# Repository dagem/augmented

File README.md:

# Augmented
an hhkb style keyboard with an added macro row

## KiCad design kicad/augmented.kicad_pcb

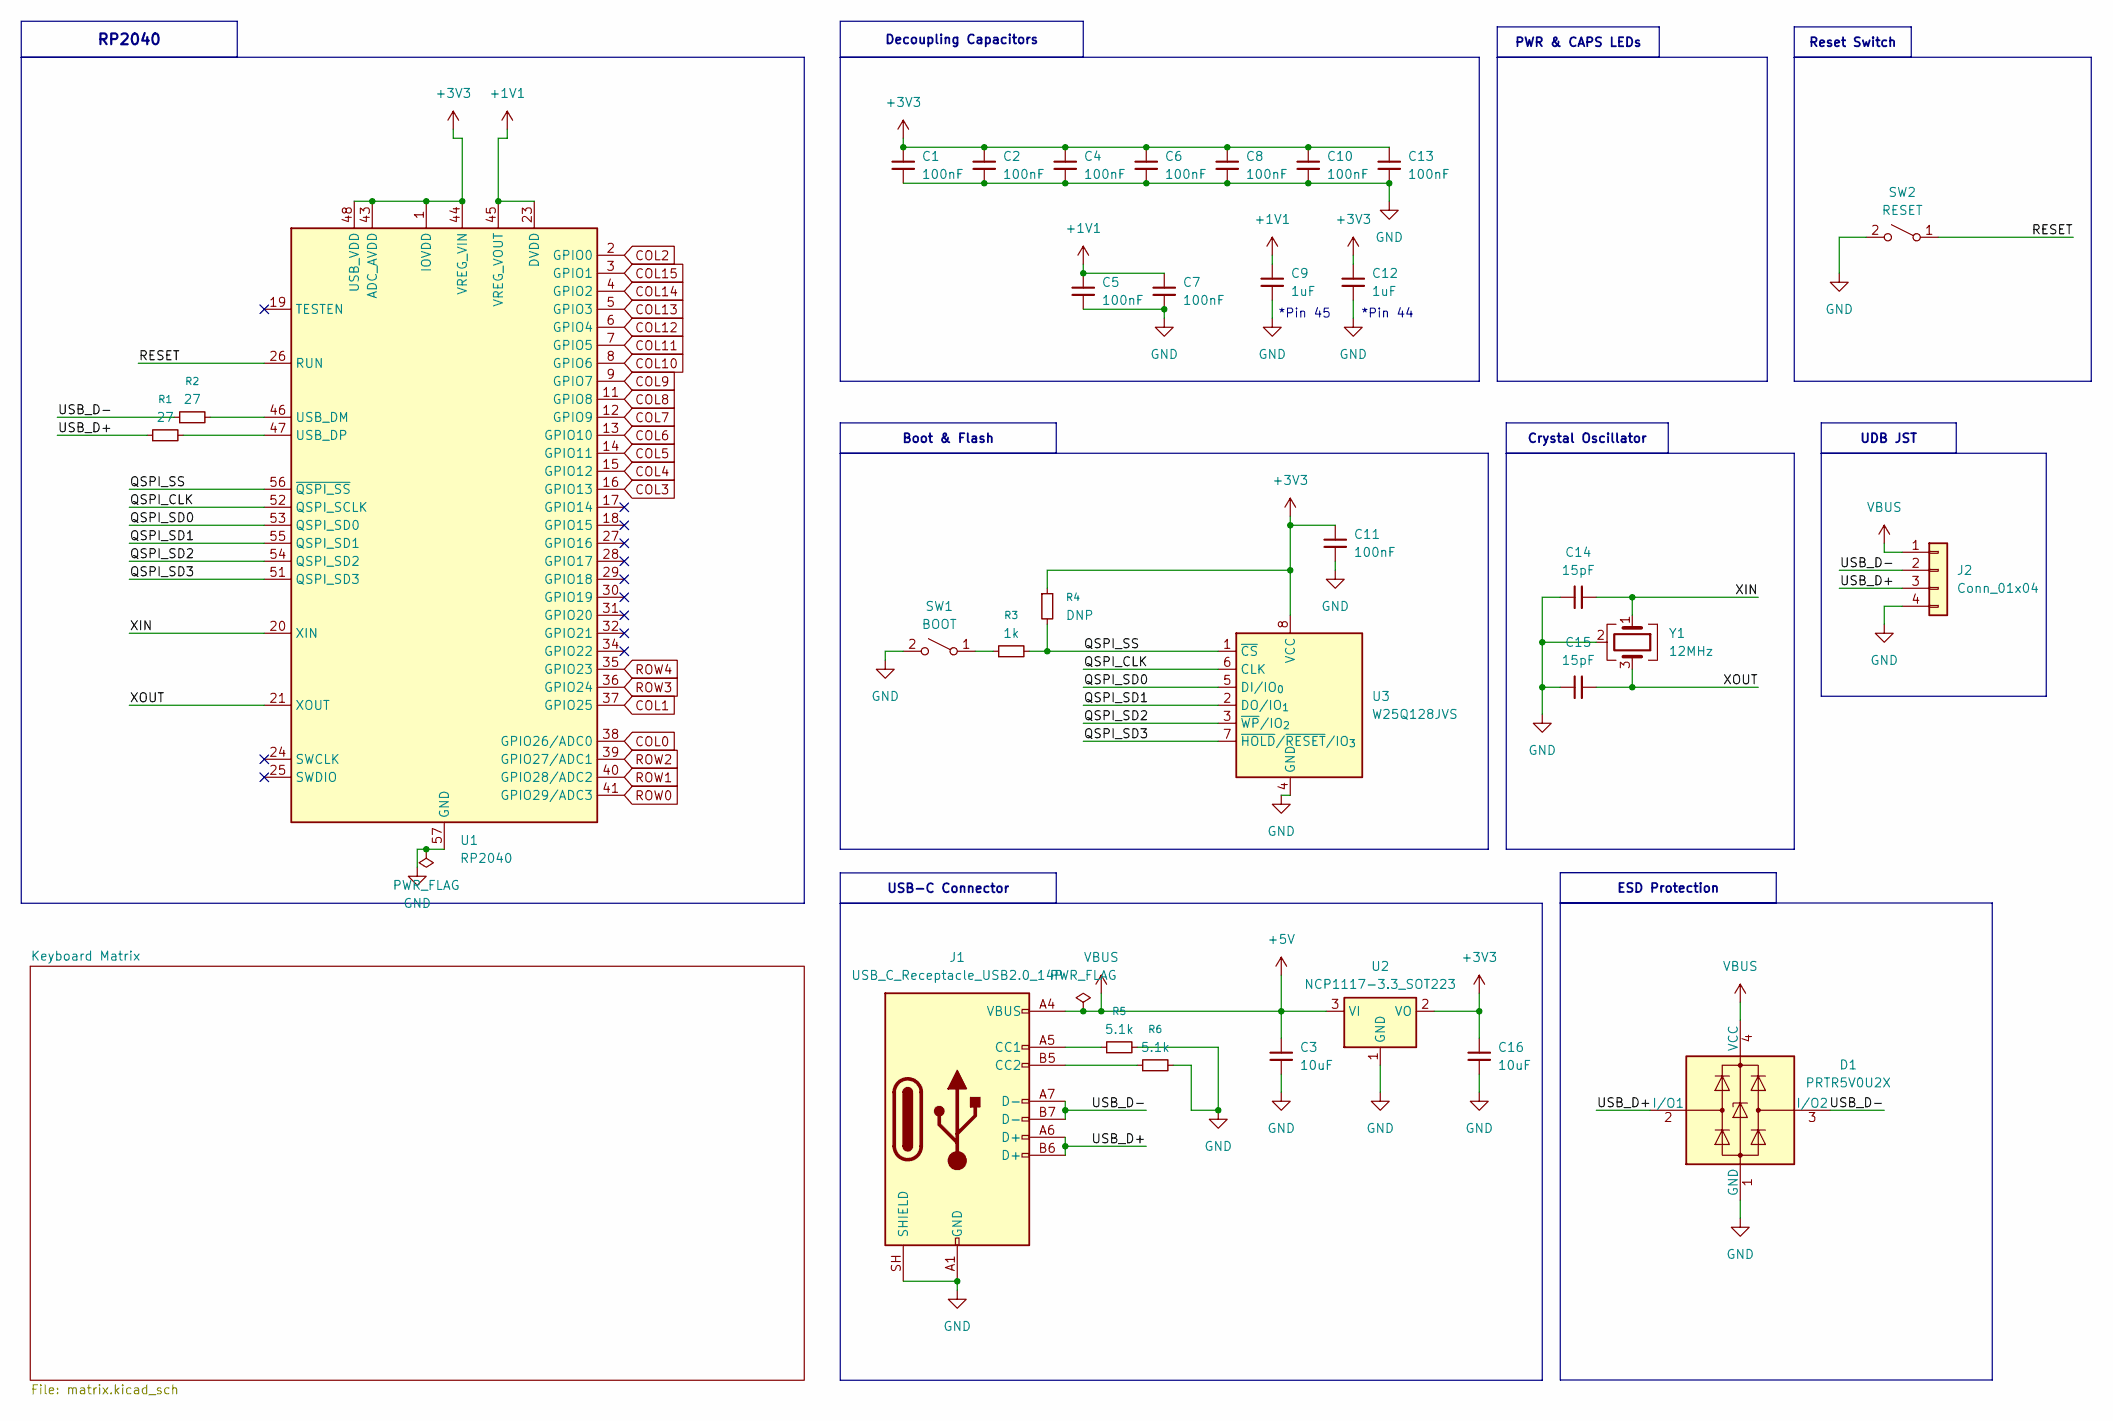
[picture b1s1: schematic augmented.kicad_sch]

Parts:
C1, C2, C4, C5, C6, C7, C8, C10, C11, C13: 100nF; C_0402_1005Metric
C3, C16: 10uF; C_0402_1005Metric
C9, C12: 1uF; C_0402_1005Metric
C14, C15: 15pF; C_0402_1005Metric
D1: PRTR5V0U2X; SOT-143
J1: USB_C_Receptacle_USB2.0_14P; USB_C_Receptacle_HRO_TYPE-C-31-M-12
J2: Conn_01x04; JST_GH_SM04B-GHS-TB_1x04-1MP_P1.25mm_Horizontal
R1, R2: 27; R_0402_1005Metric
R3: 1k; R_0402_1005Metric
R4: DNP; R_0402_1005Metric
R5, R6: 5.1k; R_0402_1005Metric
SW1: BOOT; SW_SPST_SKQG_WithoutStem
SW2: RESET; SW_SPST_SKQG_WithoutStem
U1: RP2040; QFN-56-1EP_7x7mm_P0.4mm_EP3.2x3.2mm
U2: NCP1117-3.3_SOT223; SOT-223-3_TabPin2
U3: W25Q128JVS; SOIC-8_5.3x5.3mm_P1.27mm
Y1: 12MHz; Crystal_SMD_Abracon_ABM8AIG-4Pin_3.2x2.5mm

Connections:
+1V1: C5.1, C7.1, C9.1, U1.23 (DVDD), U1.45 (VREG_VOUT), U1.50 (DVDD)
+3V3: C1.1, C2.1, C4.1, C6.1, C8.1, C10.1, C11.1, C12.1, C13.1, C16.1, R4.1, U1.1 (IOVDD), U1.10 (IOVDD), U1.22 (IOVDD), U1.33 (IOVDD), U1.42 (IOVDD), U1.43 (ADC_AVDD), U1.44 (VREG_VIN), U1.48 (USB_VDD), U1.49 (IOVDD), U2.2 (VO), U3.8 (VCC)
+5V: C3.1, D1.4 (VCC), J1.A4 (VBUS), J1.A9 (VBUS), J1.B4 (VBUS), J1.B9 (VBUS), J2.1, U2.3 (VI)
/QSPI_CLK: U1.52 (QSPI_SCLK), U3.6 (CLK)
/QSPI_SD0: U1.53 (QSPI_SD0), U3.5 (DI/IO_{0})
/QSPI_SD1: U1.55 (QSPI_SD1), U3.2 (DO/IO_{1})
/QSPI_SD2: U1.54 (QSPI_SD2), U3.3 (~WP/IO_{2})
/QSPI_SD3: U1.51 (QSPI_SD3), U3.7 (~HOLD/~RESET/IO_{3})
/QSPI_SS: R3.2, R4.2, U1.56 (~QSPI_SS), U3.1 (~CS)
/RESET: SW2.1 (A), U1.26 (RUN)
/USB_D+: D1.2 (I/O1), J1.A6 (D+), J1.B6 (D+), J2.3, R1.1
/USB_D-: D1.3 (I/O2), J1.A7 (D-), J1.B7 (D-), J2.2, R2.1
/XIN: C14.2, U1.20 (XIN), Y1.1
/XOUT: C15.2, U1.21 (XOUT), Y1.3
COL0: U1.38 (GPIO26/ADC0); also elsewhere on the board
COL1: U1.37 (GPIO25); also elsewhere on the board
COL2: U1.2 (GPIO0); also elsewhere on the board
COL3: U1.16 (GPIO13); also elsewhere on the board
COL4: U1.15 (GPIO12); also elsewhere on the board
COL5: U1.14 (GPIO11); also elsewhere on the board
COL6: U1.13 (GPIO10); also elsewhere on the board
COL7: U1.12 (GPIO9); also elsewhere on the board
COL8: U1.11 (GPIO8); also elsewhere on the board
COL9: U1.9 (GPIO7); also elsewhere on the board
COL10: U1.8 (GPIO6); also elsewhere on the board
COL11: U1.7 (GPIO5); also elsewhere on the board
COL12: U1.6 (GPIO4); also elsewhere on the board
COL13: U1.5 (GPIO3); also elsewhere on the board
COL14: U1.4 (GPIO2); also elsewhere on the board
COL15: U1.3 (GPIO1); also elsewhere on the board
GND: C1.2, C2.2, C3.2, C4.2, C5.2, C6.2, C7.2, C8.2, C9.2, C10.2, C11.2, C12.2, C13.2, C14.1, C15.1, C16.2, D1.1 (GND), J1.A1 (GND), J1.A12 (GND), J1.B1 (GND), J1.B12 (GND), J1.SH (SHIELD), J2.4, R5.2, R6.2, SW1.2 (B), SW2.2 (B), U1.57 (GND), U2.1 (GND), U3.4 (GND), Y1.2 (G), Y1.4 (G)
unnamed: J1.A5 (CC1), R5.1
unnamed: J1.B5 (CC2), R6.1
unnamed: R3.1, SW1.1 (A)
unnamed: R2.2, U1.46 (USB_DM)
unnamed: R1.2, U1.47 (USB_DP)
ROW0: U1.41 (GPIO29/ADC3); also elsewhere on the board
ROW1: U1.40 (GPIO28/ADC2); also elsewhere on the board
ROW2: U1.39 (GPIO27/ADC1); also elsewhere on the board
ROW3: U1.36 (GPIO24); also elsewhere on the board
ROW4: U1.35 (GPIO23); also elsewhere on the board

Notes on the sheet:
*Pin 44
*Pin 45
Boot & Flash
Crystal Oscillator
ESD Protection
USB-C Connector
Reset Switch
PWR & CAPS LEDs
RP2040
UDB JST
Decoupling Capacitors

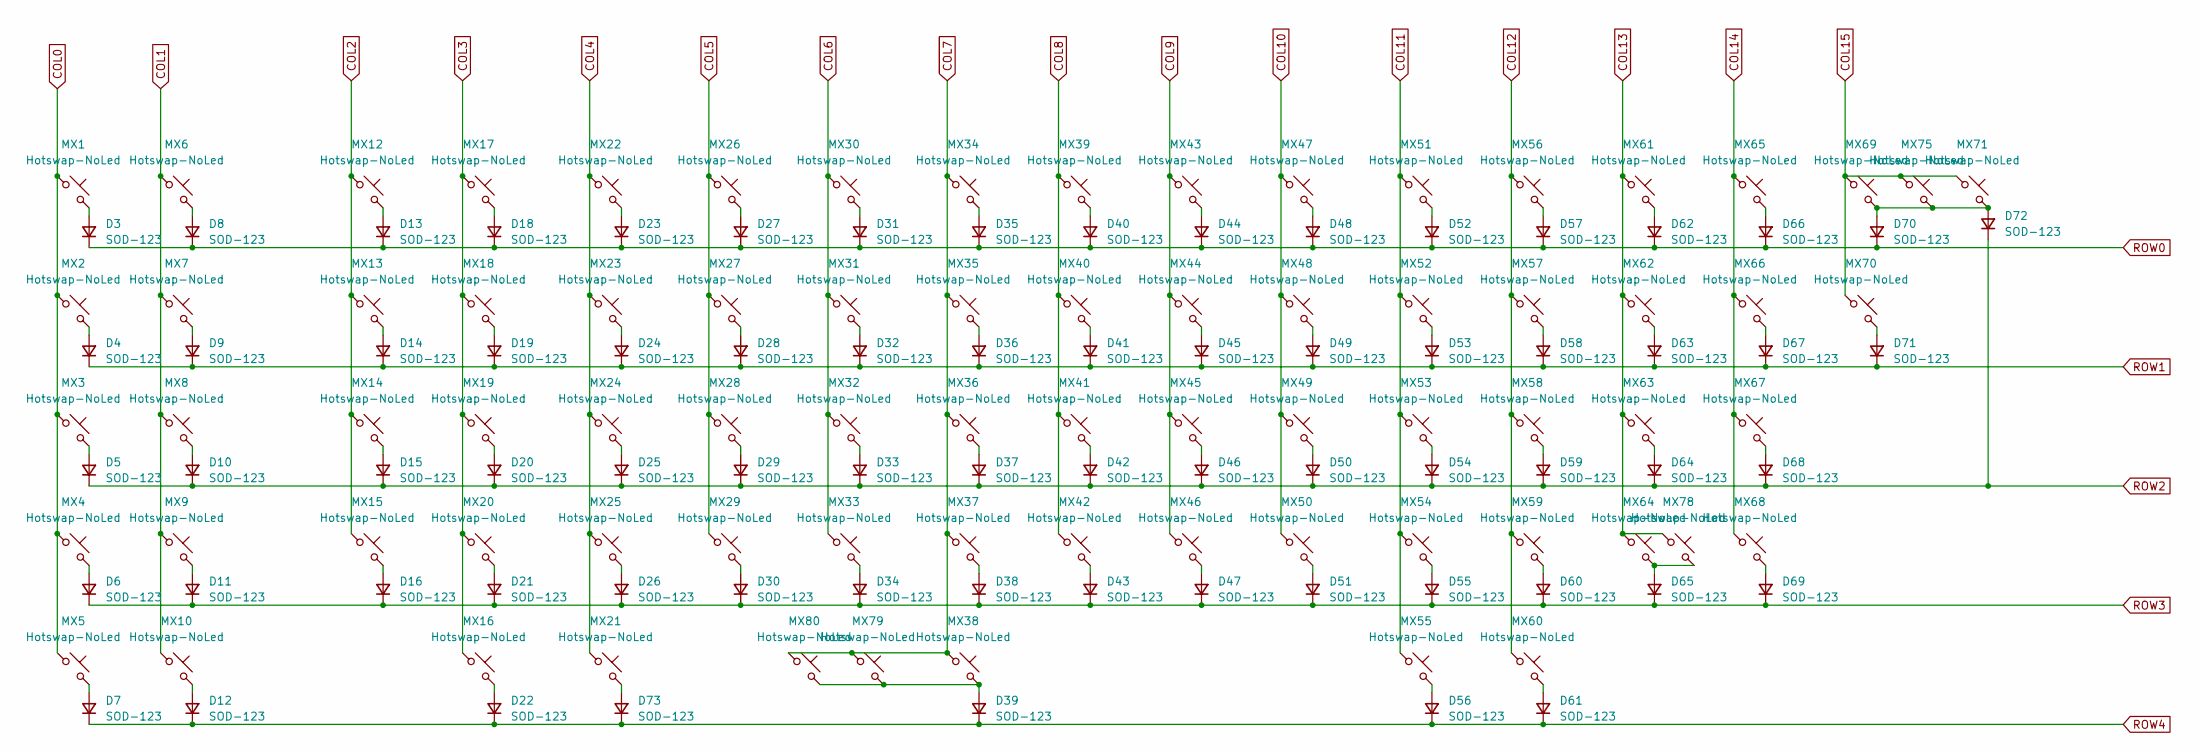
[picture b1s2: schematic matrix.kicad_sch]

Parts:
D3, D4, D5, D6, D7, D8, D9, D10, D11, D12, D13, D14, D15, D16, D18, D19, D20, D21, D22, D23, D24, D25, D26, D27, D28, D29, D30, D31, D32, D33, D34, D35, D36, D37, D38, D39, D40, D41, D42, D43, D44, D45, D46, D47, D48, D49, D50, D51, D52, D53, D54, D55, D56, D57, D58, D59, D60, D61, D62, D63, D64, D65, D66, D67, D68, D69, D70, D71, D72, D73: SOD-123; D_SOD-123
MX1, MX2, MX3, MX4, MX5, MX6, MX7, MX8, MX9, MX10, MX12, MX16, MX17, MX18, MX19, MX20, MX22, MX23, MX24, MX25, MX26, MX27, MX28, MX29, MX30, MX31, MX32, MX33, MX34, MX35, MX36, MX37, MX39, MX40, MX41, MX42, MX43, MX44, MX45, MX46, MX47, MX48, MX49, MX50, MX51, MX52, MX53, MX54, MX56, MX57, MX58, MX59, MX60, MX61, MX62, MX63, MX65, MX66, MX68, MX69, MX71: Hotswap-NoLed; MX-Hotswap-1U
MX13, MX21, MX55, MX70: Hotswap-NoLed; MX-Hotswap-1.5U
MX14, MX64: Hotswap-NoLed; MX-Hotswap-1.75U
MX15, MX67: Hotswap-NoLed; MX-Hotswap-2.25U
MX38: Hotswap-NoLed; MX-Hotswap-6U
MX75: Hotswap-NoLed; MX-Hotswap-2U
MX78: Hotswap-NoLed; MX-Hotswap-2.75U
MX79, MX80: Hotswap-NoLed; MX-Hotswap-3U

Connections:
COL0: MX1.1, MX2.1, MX3.1, MX4.1, MX5.1; also elsewhere on the board
COL1: MX6.1, MX7.1, MX8.1, MX9.1, MX10.1; also elsewhere on the board
COL2: MX12.1, MX13.1, MX14.1, MX15.1; also elsewhere on the board
COL3: MX16.1, MX17.1, MX18.1, MX19.1, MX20.1; also elsewhere on the board
COL4: MX21.1, MX22.1, MX23.1, MX24.1, MX25.1; also elsewhere on the board
COL5: MX26.1, MX27.1, MX28.1, MX29.1; also elsewhere on the board
COL6: MX30.1, MX31.1, MX32.1, MX33.1; also elsewhere on the board
COL7: MX34.1, MX35.1, MX36.1, MX37.1, MX38.1, MX79.1, MX80.1; also elsewhere on the board
COL8: MX39.1, MX40.1, MX41.1, MX42.1; also elsewhere on the board
COL9: MX43.1, MX44.1, MX45.1, MX46.1; also elsewhere on the board
COL10: MX47.1, MX48.1, MX49.1, MX50.1; also elsewhere on the board
COL11: MX51.1, MX52.1, MX53.1, MX54.1, MX55.1; also elsewhere on the board
COL12: MX56.1, MX57.1, MX58.1, MX59.1, MX60.1; also elsewhere on the board
COL13: MX61.1, MX62.1, MX63.1, MX64.1, MX78.1; also elsewhere on the board
COL14: MX65.1, MX66.1, MX67.1, MX68.1; also elsewhere on the board
COL15: MX69.1, MX70.1, MX71.1, MX75.1; also elsewhere on the board
unnamed: D3.2 (A), MX1.2
unnamed: D4.2 (A), MX2.2
unnamed: D5.2 (A), MX3.2
unnamed: D6.2 (A), MX4.2
unnamed: D7.2 (A), MX5.2
unnamed: D8.2 (A), MX6.2
unnamed: D9.2 (A), MX7.2
unnamed: D10.2 (A), MX8.2
unnamed: D11.2 (A), MX9.2
unnamed: D12.2 (A), MX10.2
unnamed: D13.2 (A), MX12.2
unnamed: D14.2 (A), MX13.2
unnamed: D15.2 (A), MX14.2
unnamed: D16.2 (A), MX15.2
unnamed: D18.2 (A), MX17.2
unnamed: D19.2 (A), MX18.2
unnamed: D20.2 (A), MX19.2
unnamed: D21.2 (A), MX20.2
unnamed: D22.2 (A), MX16.2
unnamed: D23.2 (A), MX22.2
unnamed: D24.2 (A), MX23.2
unnamed: D25.2 (A), MX24.2
unnamed: D26.2 (A), MX25.2
unnamed: D27.2 (A), MX26.2
unnamed: D28.2 (A), MX27.2
unnamed: D29.2 (A), MX28.2
unnamed: D30.2 (A), MX29.2
unnamed: D31.2 (A), MX30.2
unnamed: D32.2 (A), MX31.2
unnamed: D33.2 (A), MX32.2
unnamed: D34.2 (A), MX33.2
unnamed: D35.2 (A), MX34.2
unnamed: D36.2 (A), MX35.2
unnamed: D37.2 (A), MX36.2
unnamed: D38.2 (A), MX37.2
unnamed: D39.2 (A), MX38.2, MX79.2, MX80.2
unnamed: D40.2 (A), MX39.2
unnamed: D41.2 (A), MX40.2
unnamed: D42.2 (A), MX41.2
unnamed: D43.2 (A), MX42.2
unnamed: D44.2 (A), MX43.2
unnamed: D45.2 (A), MX44.2
unnamed: D46.2 (A), MX45.2
unnamed: D47.2 (A), MX46.2
unnamed: D48.2 (A), MX47.2
unnamed: D49.2 (A), MX48.2
unnamed: D50.2 (A), MX49.2
unnamed: D51.2 (A), MX50.2
unnamed: D52.2 (A), MX51.2
unnamed: D53.2 (A), MX52.2
unnamed: D54.2 (A), MX53.2
unnamed: D55.2 (A), MX54.2
unnamed: D56.2 (A), MX55.2
unnamed: D57.2 (A), MX56.2
unnamed: D58.2 (A), MX57.2
unnamed: D59.2 (A), MX58.2
unnamed: D60.2 (A), MX59.2
unnamed: D61.2 (A), MX60.2
unnamed: D62.2 (A), MX61.2
unnamed: D63.2 (A), MX62.2
unnamed: D64.2 (A), MX63.2
unnamed: D65.2 (A), MX64.2, MX78.2
unnamed: D66.2 (A), MX65.2
unnamed: D67.2 (A), MX66.2
unnamed: D68.2 (A), MX67.2
unnamed: D69.2 (A), MX68.2
unnamed: D70.2 (A), D72.2 (A), MX69.2, MX71.2, MX75.2
unnamed: D71.2 (A), MX70.2
unnamed: D73.2 (A), MX21.2
ROW0: D3.1 (K), D8.1 (K), D13.1 (K), D18.1 (K), D23.1 (K), D27.1 (K), D31.1 (K), D35.1 (K), D40.1 (K), D44.1 (K), D48.1 (K), D52.1 (K), D57.1 (K), D62.1 (K), D66.1 (K), D70.1 (K); also elsewhere on the board
ROW1: D4.1 (K), D9.1 (K), D14.1 (K), D19.1 (K), D24.1 (K), D28.1 (K), D32.1 (K), D36.1 (K), D41.1 (K), D45.1 (K), D49.1 (K), D53.1 (K), D58.1 (K), D63.1 (K), D67.1 (K), D71.1 (K); also elsewhere on the board
ROW2: D5.1 (K), D10.1 (K), D15.1 (K), D20.1 (K), D25.1 (K), D29.1 (K), D33.1 (K), D37.1 (K), D42.1 (K), D46.1 (K), D50.1 (K), D54.1 (K), D59.1 (K), D64.1 (K), D68.1 (K), D72.1 (K); also elsewhere on the board
ROW3: D6.1 (K), D11.1 (K), D16.1 (K), D21.1 (K), D26.1 (K), D30.1 (K), D34.1 (K), D38.1 (K), D43.1 (K), D47.1 (K), D51.1 (K), D55.1 (K), D60.1 (K), D65.1 (K), D69.1 (K); also elsewhere on the board
ROW4: D7.1 (K), D12.1 (K), D22.1 (K), D39.1 (K), D56.1 (K), D61.1 (K), D73.1 (K); also elsewhere on the board

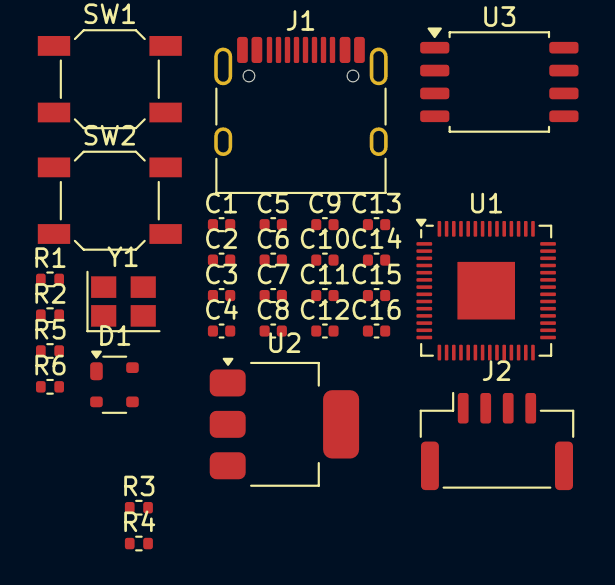
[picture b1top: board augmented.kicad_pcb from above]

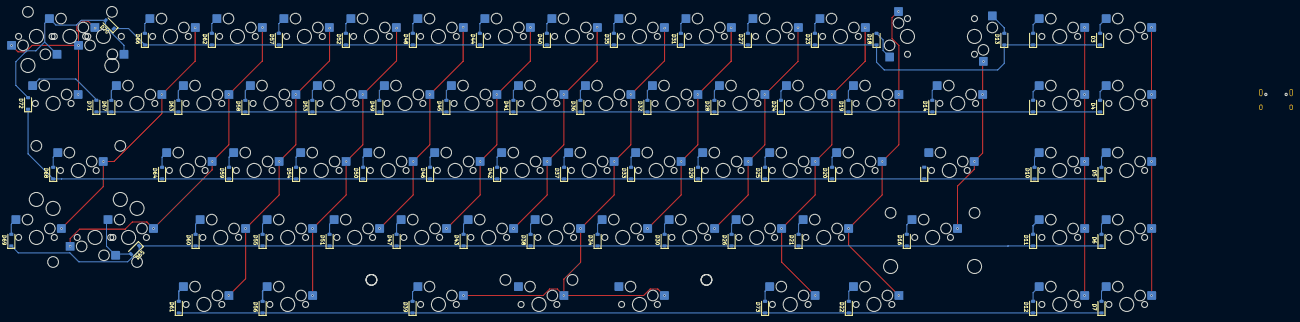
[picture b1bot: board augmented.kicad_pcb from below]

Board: 2 copper layers, 175 parts (144 on the bottom side), 110 nets.

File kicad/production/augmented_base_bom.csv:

Designator,Footprint,Quantity,Value,LCSC Part #
"C1, C10, C11, C13, C2, C4, C5, C6, C7, C8",0603,10,100nF,
"C12, C9",0603,2,1uF,
"C14, C15",0603,2,15pF,
D1,LED_miniPLCC_2315_Handsoldering,1,RED,
"D13, D14, D15, D16, D17, D18, D19, D20, D21, D22, D23, D24, D25, D26, D27, D28, D29, D30, D31, D32, D33, D34, D35, D36, D37, D38, D39, D40, D41, D42, D43, D44, D45, D46, D47, D48, D49, D50, D51, D52, D53, D54, D55, D56, D57, D58, D59, D60, D61, D62, D63, D64, D65, D66, D67, D68, D69, D70, D71, D72",D_SOD-123,60,SOD-123,
D2,LED_miniPLCC_2315_Handsoldering,1,WHITE,
J2,JST_GH_SM04B-GHS-TB_1x04-1MP_P1.25mm_Horizontal,1,Conn_01x04,
J3,TE_0-1734839-7_1x07-1MP_P0.5mm_Horizontal,1,Conn_01x07,
"MX11, MX14, MX64",MX-Hotswap-1.75U,3,Hotswap-NoLed,
"MX12, MX16, MX17, MX18, MX19, MX20, MX22, MX23, MX24, MX25, MX26, MX27, MX28, MX29, MX30, MX31, MX32, MX33, MX34, MX35, MX36, MX37, MX39, MX40, MX41, MX42, MX43, MX44, MX45, MX46, MX47, MX48, MX49, MX50, MX51, MX52, MX53, MX54, MX56, MX57, MX58, MX59, MX60, MX61, MX62, MX63, MX65, MX66, MX68, MX69, MX71",MX-Hotswap-1U,51,Hotswap-NoLed,
"MX13, MX21, MX55, MX70",MX-Hotswap-1.5U,4,Hotswap-NoLed,
"MX15, MX67",MX-Hotswap-2.25U,2,Hotswap-NoLed,
MX38,MX-Hotswap-6U-ReversedStabilizers,1,Hotswap-NoLed,
"R1, R2",0603,2,27,
"R3, R7, R8",0603,3,1k,
R4,0603,1,DNP,
SW1,SW_SPST_SKQG_WithoutStem,1,BOOT,
SW2,SW_SPST_SKQG_WithoutStem,1,RESET,
U1,QFN-56-1EP_7x7mm_P0.4mm_EP3.2x3.2mm,1,RP2040,
U3,SOIC-8_5.3x5.3mm_P1.27mm,1,W25Q128JVS,
Y1,Crystal_SMD_Abracon_ABM8AIG-4Pin_3.2x2.5mm,1,12MHz,
